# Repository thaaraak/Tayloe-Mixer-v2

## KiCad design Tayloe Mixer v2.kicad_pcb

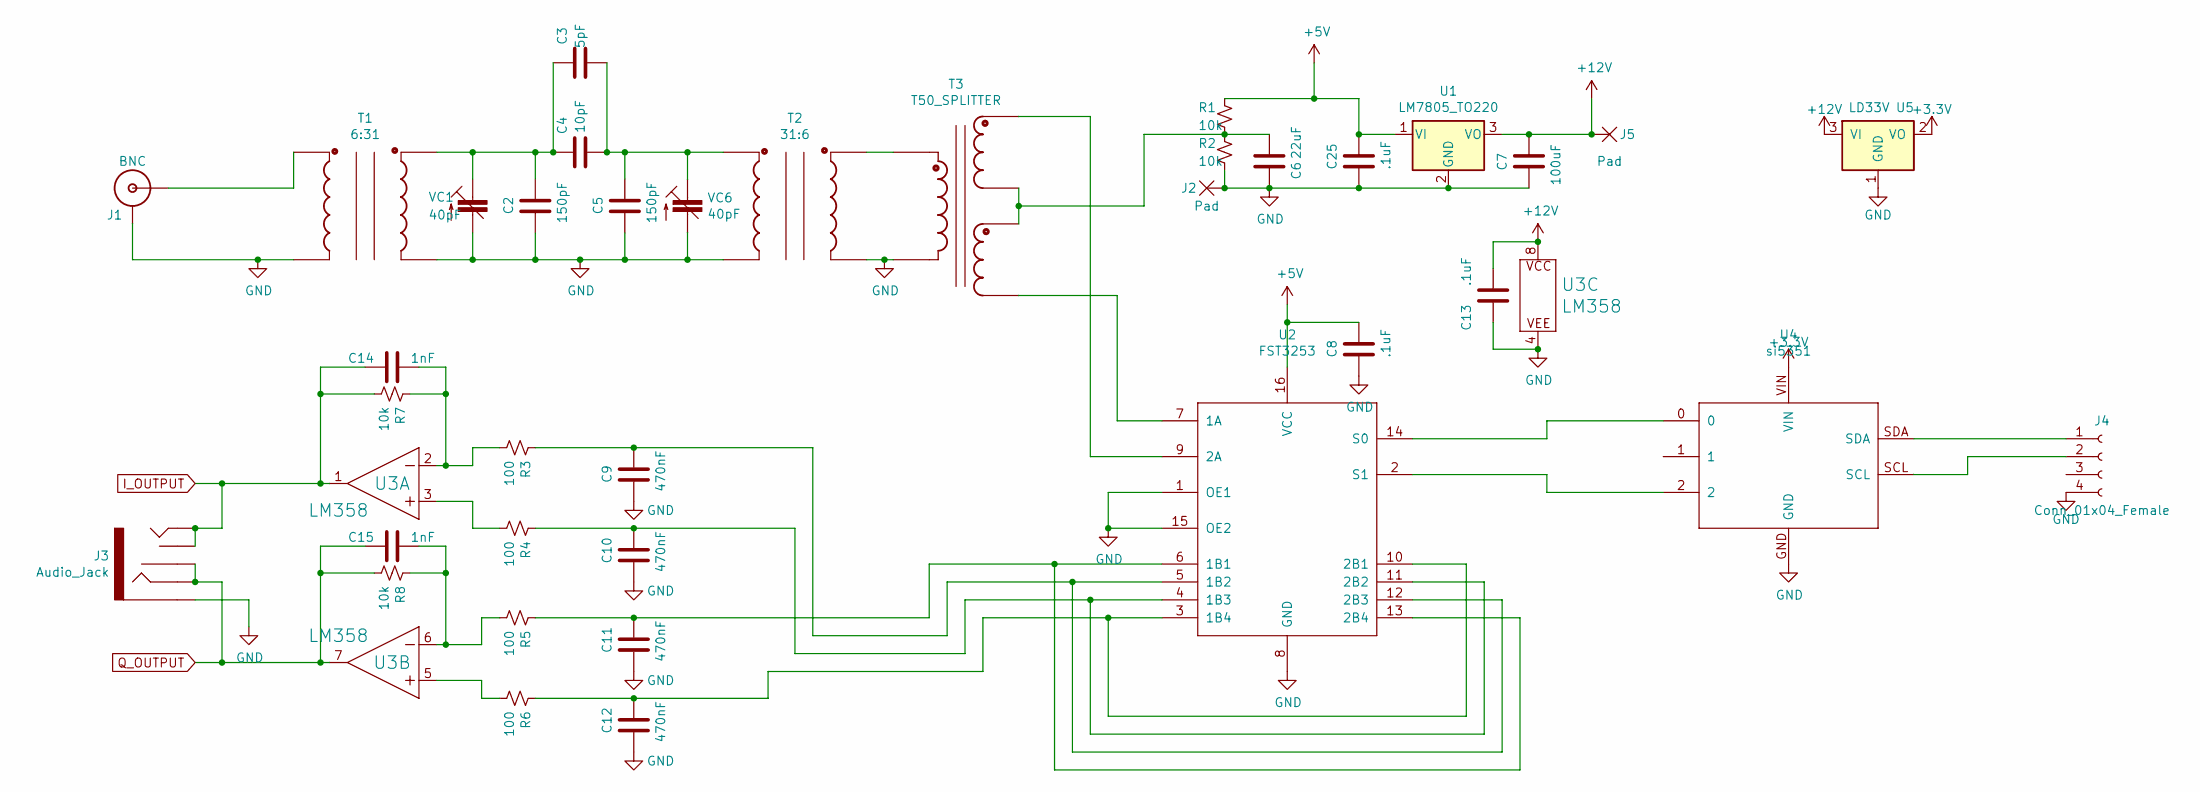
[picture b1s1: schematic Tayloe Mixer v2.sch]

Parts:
C2, C5: 150pF; Capacitor 1206
C3: 5pF; Capacitor 1206
C4: 10pF; Capacitor 1206
C6: 22uF; CP_Elec_4x5.4
C7: 100uF; CP_Elec_6.3x5.4
C8, C13, C25: .1uF; Capacitor 1206
C9, C10, C11, C12: 470nF; Capacitor 0805
C14, C15: 1nF; Capacitor 0805
J1: BNC
J2, J5: Pad
J3: Audio_Jack
J4: Conn_01x04_Female; PinHeader_1x04_P2.54mm_Vertical
R1, R2, R7, R8: 10k; Capacitor 0805
R3, R4, R5, R6: 100; Capacitor 0805
T1: 6:31; T37 Transformer
T2: 31:6; T37 Transformer
T3: T50_SPLITTER; T50 Trifilar
U1: LM7805_TO220; TO-220-3_Vertical
U2: FST3253; SO16
U3: LM358; SOIC8
U4: si5351
U5: LD33V; TO-220-3_Vertical
VC1, VC6: 40pF; trimcap

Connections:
+3V3: U4.VIN, U5.2 (VO)
+5V: C8.2, C25.2, R1.1, U1.1 (VI), U2.16 (VCC)
+12V: C7.1, C13.2, J5.1, U1.3 (VO), U3.8 (P$V+), U5.3 (VI)
GND: C2.1, C5.1, C6.2, C7.2, C8.1, C9.1, C10.1, C11.1, C12.1, C13.1, C25.1, J1.GND, J2.1, J3.SLEEVE, J4.4, R2.2, T1.C1A, T1.C2A, T2.C1A, T2.C2A, T3.C1A, U1.2 (GND), U2.1 (OE1), U2.8 (GND), U2.15 (OE2), U3.4 (P$V-), U4.GND, U5.1 (GND), VC1.2 (A), VC6.2 (A)
I_OUTPUT: C14.1, J3.TIP, J3.TSH, R7.2, U3.1 (OUT)
unnamed: C2.2, C3.1, C4.1, T1.C2B, VC1.1 (E)
unnamed: C3.2, C4.2, C5.2, T2.C1B, VC6.1 (E)
unnamed: C6.1, R1.2, R2.1, T3.C2A, T3.C3B
unnamed: C9.2, R3.1, U2.5 (1B2), U2.12 (2B3)
unnamed: C10.2, R4.1, U2.4 (1B3), U2.11 (2B2)
unnamed: C11.2, R5.1, U2.6 (1B1), U2.13 (2B4)
unnamed: C12.2, R6.1, U2.3 (1B4), U2.10 (2B1)
unnamed: C14.2, R3.2, R7.1, U3.2 (-IN)
unnamed: C15.2, R5.2, R8.1, U3.6 (-IN)
unnamed: J1.S (OUT), T1.C1B
unnamed: J4.1, U4.SDA
unnamed: J4.2, U4.SCL
unnamed: R4.2, U3.3 (+IN)
unnamed: R6.2, U3.5 (+IN)
unnamed: T2.C2B, T3.C1B
unnamed: T3.C2B, U2.9 (2A)
unnamed: T3.C3A, U2.7 (1A)
unnamed: U2.2 (S1), U4.2
unnamed: U2.14 (S0), U4.0
Q_OUTPUT: C15.1, J3.RING, J3.RSH, R8.2, U3.7 (OUT)

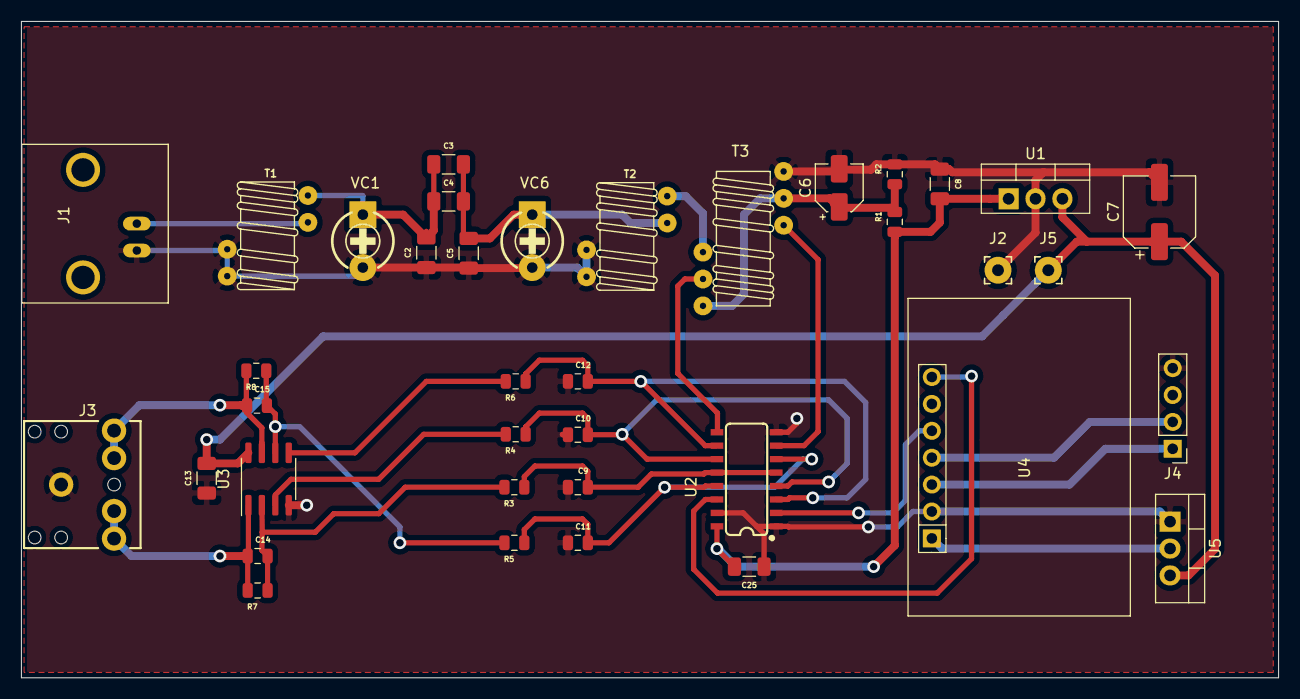
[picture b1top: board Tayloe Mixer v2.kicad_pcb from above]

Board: 2 copper layers, 118.8 x 62.0 mm, 38 parts (0 on the bottom side), 25 nets.

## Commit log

2020-08-26 swapping caps
2020-08-29 Added bands table
2020-08-29 added PDFs for traces
2022-06-25 rescue
